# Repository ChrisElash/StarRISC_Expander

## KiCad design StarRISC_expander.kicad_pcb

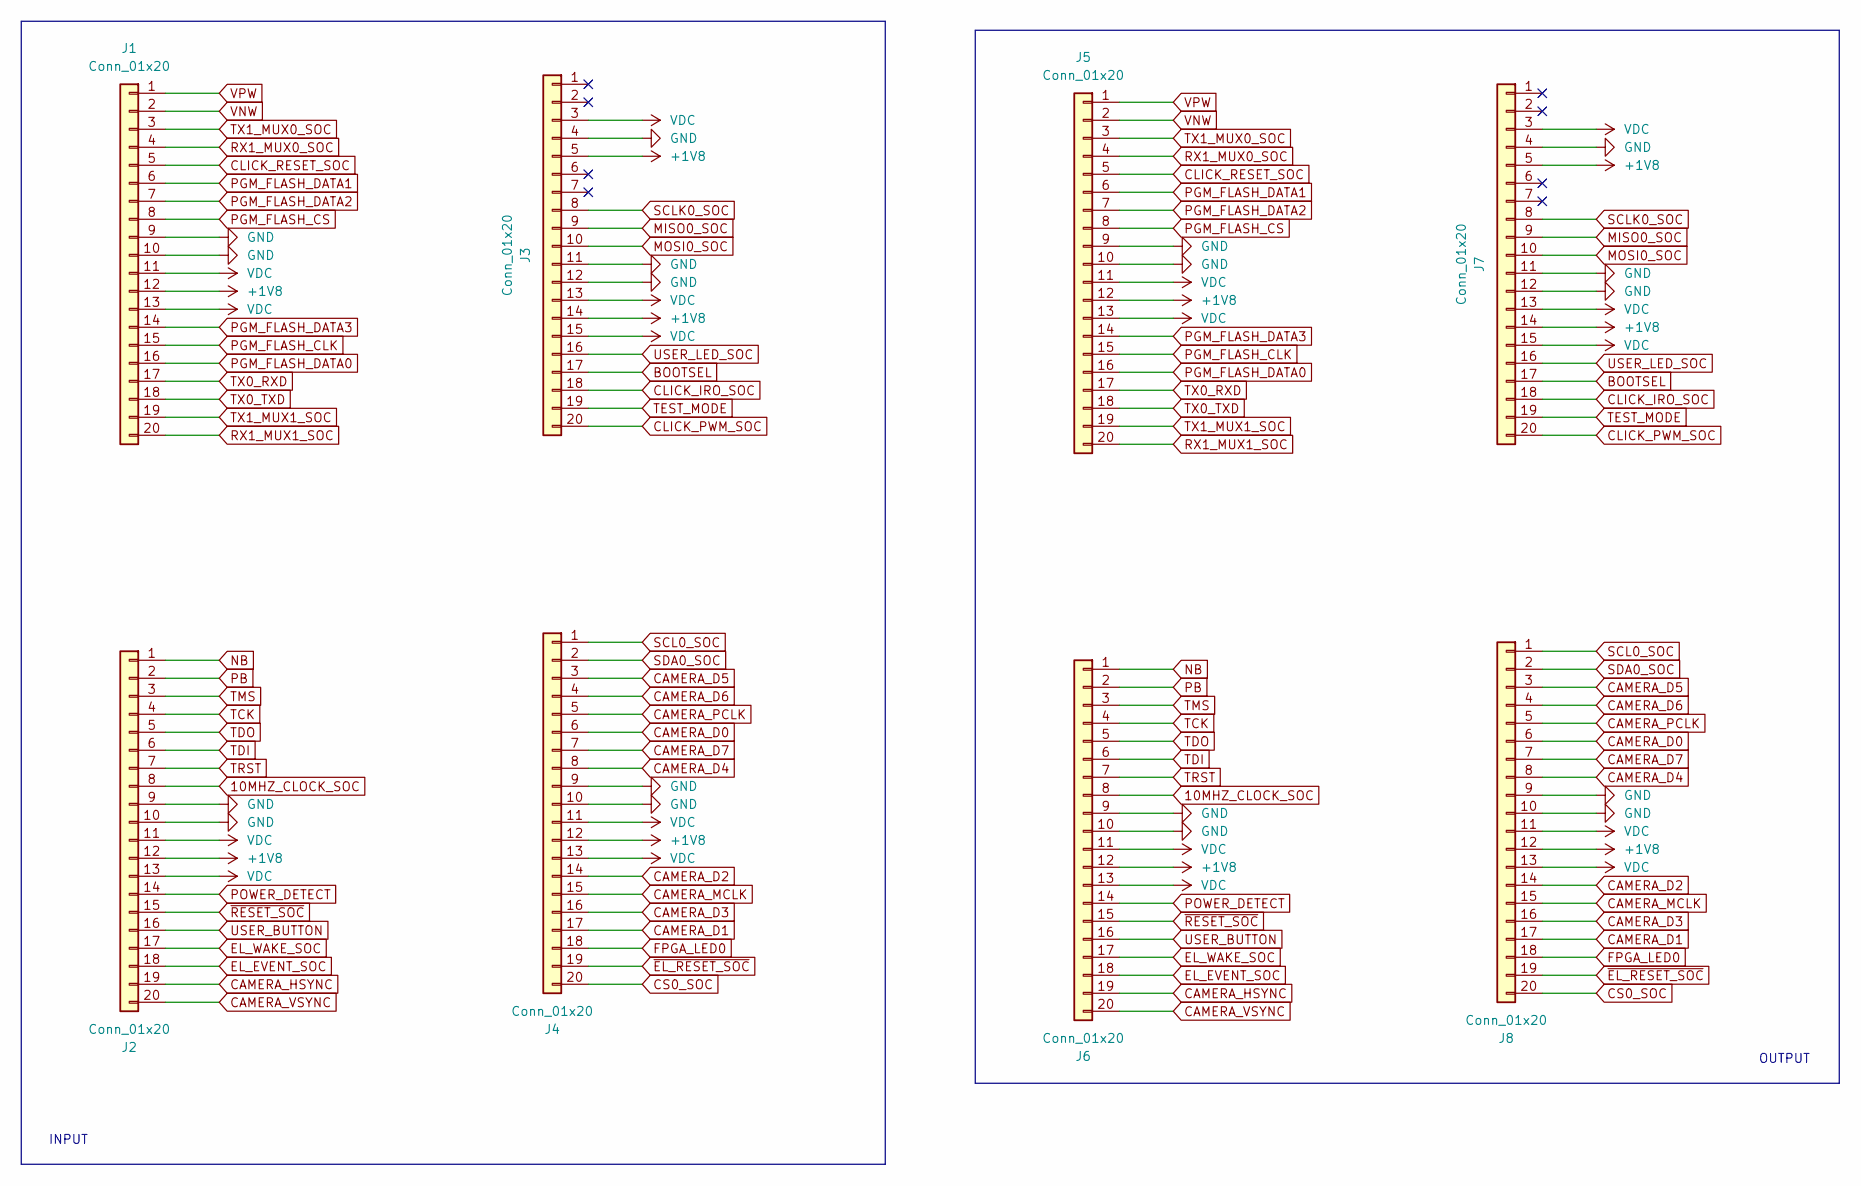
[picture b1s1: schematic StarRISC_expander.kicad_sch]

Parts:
J1, J2, J3, J4: Conn_01x20; PinSocket_1x20_P1.00mm_Vertical
J5, J6, J7, J8: Conn_01x20; PinHeader_1x20_P1.00mm_Vertical

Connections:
10MHZ_CLOCK_SOC: J2.8, J6.8
+1V8: J1.12, J2.12, J3.5, J3.14, J4.12, J5.12, J6.12, J7.5, J7.14, J8.12
BOOTSEL: J3.17, J7.17
CAMERA_D0: J4.6, J8.6
CAMERA_D1: J4.17, J8.17
CAMERA_D2: J4.14, J8.14
CAMERA_D3: J4.16, J8.16
CAMERA_D4: J4.8, J8.8
CAMERA_D5: J4.3, J8.3
CAMERA_D6: J4.4, J8.4
CAMERA_D7: J4.7, J8.7
CAMERA_HSYNC: J2.19, J6.19
CAMERA_MCLK: J4.15, J8.15
CAMERA_PCLK: J4.5, J8.5
CAMERA_VSYNC: J2.20, J6.20
CLICK_IRO_SOC: J3.18, J7.18
CLICK_PWM_SOC: J3.20, J7.20
CLICK_RESET_SOC: J1.5, J5.5
CS0_SOC: J4.20, J8.20
EL_EVENT_SOC: J2.18, J6.18
EL_WAKE_SOC: J2.17, J6.17
FPGA_LED0: J4.18, J8.18
GND: J1.9, J1.10, J2.9, J2.10, J3.4, J3.11, J3.12, J4.9, J4.10, J5.9, J5.10, J6.9, J6.10, J7.4, J7.11, J7.12, J8.9, J8.10
MISO0_SOC: J3.9, J7.9
MOSI0_SOC: J3.10, J7.10
NB: J2.1, J6.1
PB: J2.2, J6.2
PGM_FLASH_CLK: J1.15, J5.15
PGM_FLASH_CS: J1.8, J5.8
PGM_FLASH_DATA0: J1.16, J5.16
PGM_FLASH_DATA1: J1.6, J5.6
PGM_FLASH_DATA2: J1.7, J5.7
PGM_FLASH_DATA3: J1.14, J5.14
POWER_DETECT: J2.14, J6.14
RX1_MUX0_SOC: J1.4, J5.4
RX1_MUX1_SOC: J1.20, J5.20
SCL0_SOC: J4.1, J8.1
SCLK0_SOC: J3.8, J7.8
SDA0_SOC: J4.2, J8.2
TCK: J2.4, J6.4
TDI: J2.6, J6.6
TDO: J2.5, J6.5
TEST_MODE: J3.19, J7.19
TMS: J2.3, J6.3
TRST: J2.7, J6.7
TX0_RXD: J1.17, J5.17
TX0_TXD: J1.18, J5.18
TX1_MUX0_SOC: J1.3, J5.3
TX1_MUX1_SOC: J1.19, J5.19
USER_BUTTON: J2.16, J6.16
USER_LED_SOC: J3.16, J7.16
VDC: J1.11, J1.13, J2.11, J2.13, J3.3, J3.13, J3.15, J4.11, J4.13, J5.11, J5.13, J6.11, J6.13, J7.3, J7.13, J7.15, J8.11, J8.13
VNW: J1.2, J5.2
VPW: J1.1, J5.1
~EL_RESET_SOC: J4.19, J8.19
~RESET_SOC: J2.15, J6.15

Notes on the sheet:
INPUT
OUTPUT

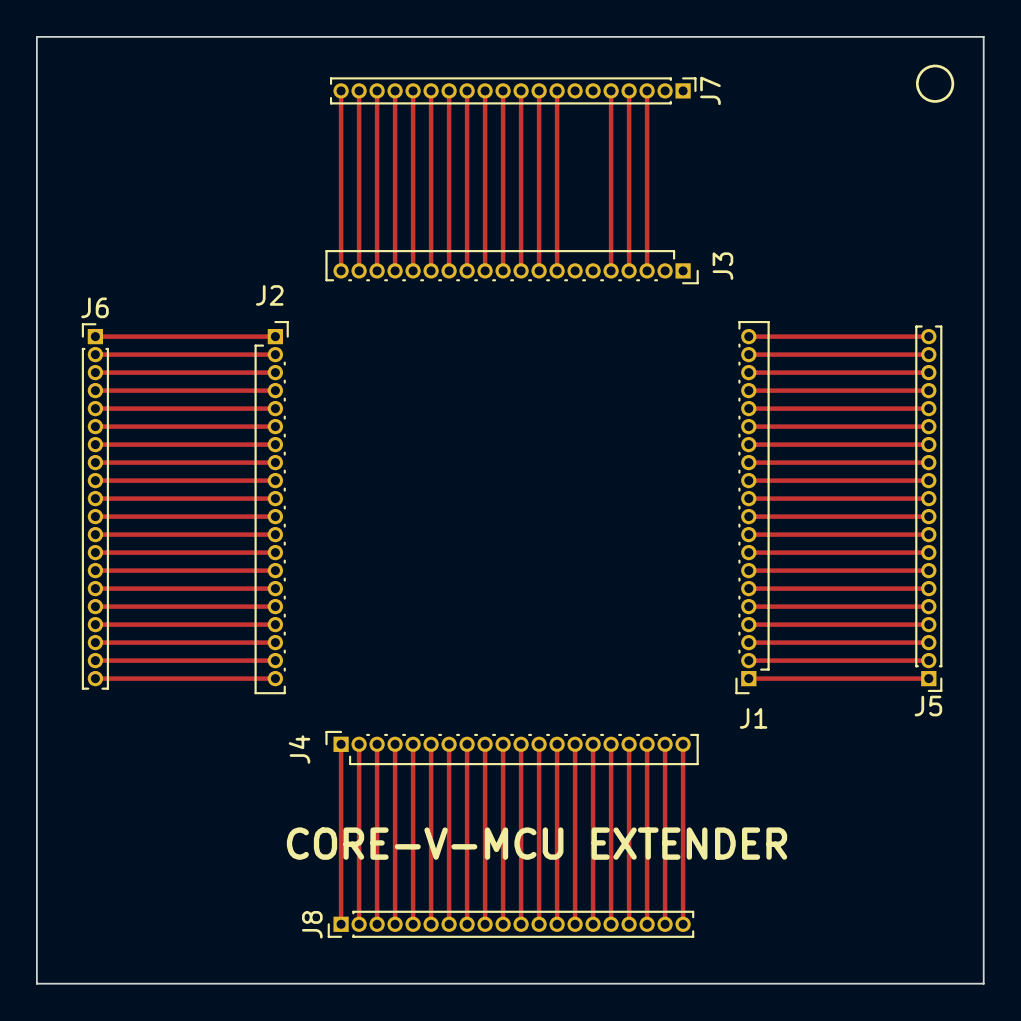
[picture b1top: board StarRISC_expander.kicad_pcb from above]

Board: 2 copper layers, 52.6 x 52.6 mm, 8 parts (0 on the bottom side), 56 nets.
